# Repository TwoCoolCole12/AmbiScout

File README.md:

# AmbiScout
A portable environment sensor to sense ambient temperature, humidity, light, movement speed, and more!

Inspired by features on the Starbie, but extended for functionality and development time. 

Living in a place where the climate constantly fluctuates, it can be handy to glance at a small device that's 
not a phone to see what's happening in the air around oneself.

Here's some of the planned features:

- [x] Temperature Sensor
- [x] Humidity Sensor
- [x] Battery Powered or Rechargeability
- [x] OLED Display
- [x] Navigation Buttons
- [x] Power/Charging Indicator
- [x] Ambient Light Level Monitor
- [x] Audio Sensor

Checks does not mean it's programmed, just accounted for and wired.

With enough work, it might be reasonable to add in these features too, but they are lower priority:

- [ ] Wi-Fi Connection
- [ ] Bluetooth Compatiblitiy
- [ ] Access to Weather Forcasts
- [ ] Push Notifications when Major Changes Occue
- [ ] Charging & Battery Info
- [ ] CO2 Sensor
- [x] Barometric Pressure Sensor
- [ ] Built in Clock
- [ ] Movement Sensor

**Hardware Specifications** WIP

* Espressif ESP32-S3-MINI-1-N8 - Chosen due to high pin number, Wi-Fi and Bluetooth connectivity, compatibility with Arduino, and low cost for the given performance
  * Pin Layout Reference: https://documentation.espressif.com/esp32-s3-mini-1_mini-1u_datasheet_en.html
* Light Dependent Resistor A1050 14 - Selected due to native support in KiCad and high sensitivity
  * Pin Reference: https://www.caretxdigital.com/cat6-ethernet-cable-amazon/
* I2C SHT31-DIS Temperature & Humidity Sensor - Chosen due to accuracy and multifunctionality
  * Pin Reference: https://www.alldatasheet.com/datasheet-pdf/view/1522466/SENSIRION/SHT31-DIS.html
* SPH0655LM4H-1-8 Sound Sensor - Chosen for compactness and price point
  * Pin Reference: https://mm.digikey.com/Volume0/opasdata/d220001/medias/docus/6634/SPH0655LM4H-1-8.pdf

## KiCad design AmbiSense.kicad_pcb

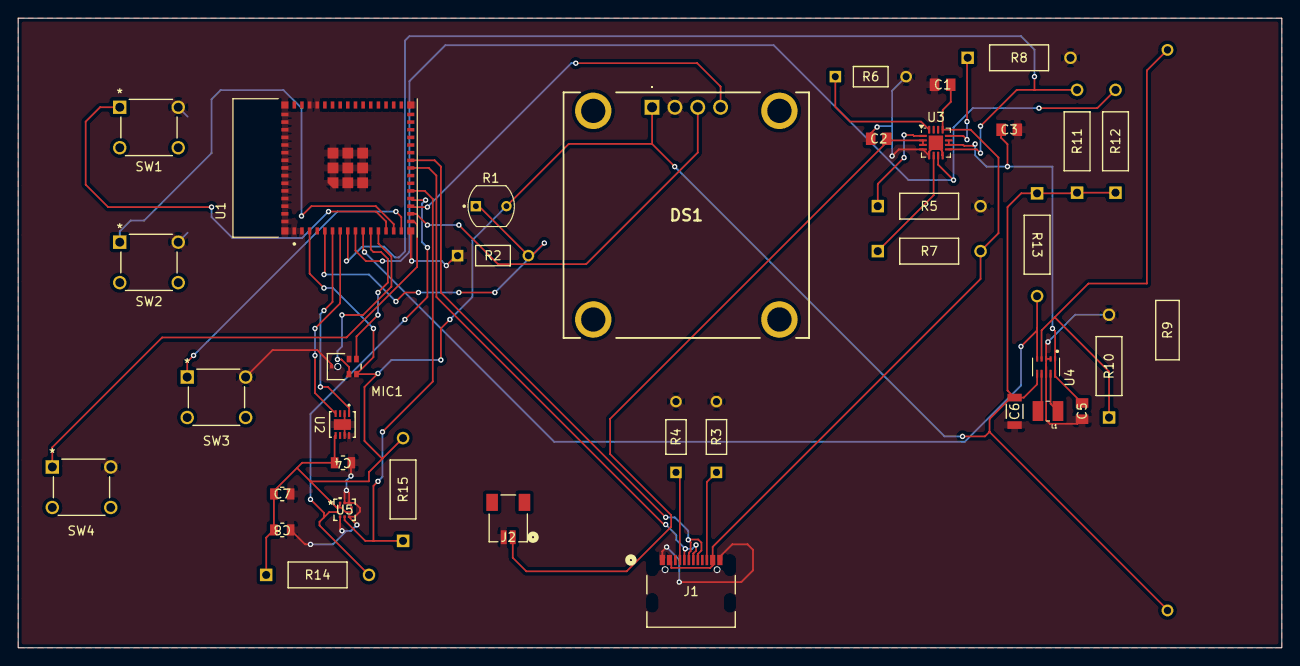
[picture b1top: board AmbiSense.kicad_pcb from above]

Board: 2 copper layers, 140.5 x 70.0 mm, 37 parts (0 on the bottom side), 32 nets.

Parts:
C1, C2, C3, C5: 10µF; Cap10UF
C4, C7, C8: 100nF; Cap100nF
C6: 22µF; Cap22UF
DS1: WEA012864DWPP3N00003
J1: USB4105-GF-A; USB4105_GCT
J2: SM02B-SRSS-TB LFSN; CONN_SM02B-SRSS-TB_JST
L1: 0.47 µH; INDC2520X120N
MIC1: SPH0655LM4H-1; SPH0655LM4H-1_KNO
R1: PDV-P8103; PHODET_PDV-P8103
R2: 100K; Res100kO
R3, R4: 5.1K; Res5.1kO
R5, R7, R11, R12, R13: 10k; Res10kO
R6: 1.8k; Res1.8kO
R8: 3k; Res3kO
R9: 511k; Res511kO
R10: 91k; Res91kO
R14, R15: 4.7kΩ; Res4.7kO
SW1, SW2, SW3, SW4: SW_Push; SW4_1825910-B_TEC
U1: ESP32-S3-MINI-1-N8; XCVR_ESP32-S3-MINI-1-N8
U2: SHT31-DIS; U_SHT3_SEN
U3: BQ24074RGT; VQFN-16-1EP_3x3mm_P0.5mm_EP1.6x1.6mm
U4: TPS63802DLAR; VREG_TPS63802DLAR
U5: BMP384; LGA10_2.0X2.0X0.95_BOS

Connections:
/3V3_POWER: C4.2, C6.2, C7.1, C8.2, DS1.1 (VCC), MIC1.5 (VDD), R1.2, R9.1, R11.1, R12.1, R13.1, R14.1, R15.2, U1.3 (3V3), U2.5 (VDD), U4.6 (VOUT), U5.1 (VDDIO), U5.6 (CSB), U5.10 (VDD)
/AUDIO_CLOCK: MIC1.4 (CLOCK), U1.12 (IO8)
/AUDIO_DATA: MIC1.1 (DATA), U1.11 (IO7)
/BAT_POS: C2.2, J2.1, U3.2 (BAT), U3.3 (BAT)
/BCK_SW: SW4.1, U1.16 (IO12)
/CHG STATUS: R11.2, U1.8 (IO4), U3.9 (~CHG)
/DOWN_SW: SW2.1, U1.14 (IO10)
/LDR_I/O: R1.1, R2.2, U1.5 (IO1)
/OLED_SCL: DS1.3 (SCL), U1.17 (IO13)
/OLED_SDA: DS1.4 (SDA), U1.18 (IO14)
/PGOOD STATUS: R12.2, U1.9 (IO5), U3.7 (~PGOOD)
/PRESS_SCL: R14.2, U1.19 (IO15), U5.2 (SCK)
/PRESS_SDA: R15.1, U1.20 (IO16), U5.4 (SDI)
/REG PGOOD: R13.2, U1.10 (IO6), U4.5 (PG)
/SEL_SW: SW3.1, U1.15 (IO11)
/SYS_PWR: C3.1, C5.2, U3.10 (OUT), U3.11 (OUT), U4.1 (EN), U4.10 (VIN)
/T&H SCL: U1.7 (IO3), U2.4 (SCL)
/T&H SDA: U1.6 (IO2), U2.1 (SDA)
/UP_SW: SW1.1, U1.13 (IO9)
/USB 5V: C1.2, J1.A4-B9 (VBUS), J1.B4-A9 (VBUS), R7.2, U3.13 (IN)
/USB D+: J1.A6 (DP1), J1.B6 (DP2), U1.24 (IO20)
/USB D-: J1.A7 (DN1), J1.B7 (DN2), U1.23 (IO19)
GND: C1.1, C2.1, C3.2, C4.1, C5.1, C6.1, C7.2, C8.1, DS1.2 (GND), J1.A1-B12 (GND), J1.B1-A12 (GND), J2.2, MIC1.3 (GROUND), R2.1, R3.2, R4.2, R5.2, R6.2, R8.2, R10.2, SW1.2, SW2.2, SW3.2, SW4.2, U1.1 (GND), U1.2 (GND), U1.42 (GND), U1.43 (GND), U1.46 (GND), U1.47 (GND), U1.48 (GND), U1.49 (GND), U1.50 (GND), U1.51 (GND), U1.52 (GND), U1.53 (GND), U1.54 (GND), U1.55 (GND), U1.56 (GND), U1.57 (GND), U1.58 (GND), U1.59 (GND), U1.60 (GND), U1.61 (GND), U1.61_1 (GND), U1.61_2 (GND), U1.61_3 (GND), U1.61_4 (GND), U1.61_5 (GND), U1.61_6 (GND), U1.61_7 (GND), U1.61_8 (GND), U1.62 (GND), U1.63 (GND), U1.64 (GND), U1.65 (GND), U2.2 (ADDR), U2.7 (R), U2.8 (VSS), U2.9 (VSS), U3.4 (~CE), U3.5 (EN2), U3.8 (VSS), U3.17 (VSS), U4.2 (MODE), U4.3 (AGND), U4.8 (GND), U5.3 (VSS), U5.5 (SDO), U5.8 (VSS), U5.9 (VSS)
unnamed: J1.A5 (CC1), R4.1
unnamed: J1.B5 (CC2), R3.1
unnamed: R7.1, U3.6 (EN1)
unnamed: R8.1, U3.12 (ILIM)
unnamed: R6.1, U3.16 (ISET)
unnamed: R5.1, U3.1 (TS)
unnamed: R9.2, R10.1, U4.4 (FB)
unnamed: L1.1, U4.9 (L1)
unnamed: L1.2, U4.7 (L2)

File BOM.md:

# AmbiScout – bill of materials

<!-- Generated by Half Life from project cmuzxkajc008201k9c68hd4dr. Edits here are overwritten on the next sync. -->
<!-- Generated: 2026-10-10T14:32:10.378Z -->

> [!NOTE]
> This parts list is mirrored from [Half Life](https://halflife.hackclub.com). Editing it here will not change the platform's copy, and the next sync overwrites this file.

| Week | Tier | Parts funding |
| --- | --- | --- |
| Week 1 | Tier 2 | $65.00 |

| Part | What it's for | Qty | Unit | Total | Vendor |
| --- | --- | --- | --- | --- | --- |
| [ESP32-S3-MINI-1-N8](https://www.digikey.com/en/products/detail/espressif-systems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 | Microcontroller as the Main Brain, Wi-Fi and Bluetooth support | 1 | $5.43 | $5.43 | [DigiKey](https://www.digikey.com/en/products/detail/espressif-systems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 |
| [SHT31-DIS-B2.5KS](https://www.digikey.com/en/products/detail/sensirion-ag/SHT3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 | Temperature & Humidity Sensor | 1 | $5.00 | $5.00 | [DigiKey](https://www.digikey.com/en/products/detail/sensirion-ag/SHT3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 |
| [WEA012864DBPP3N00003](https://www.digikey.com/en/products/detail/winstar-display/W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 | OLED Display Screen | 1 | $7.82 | $7.82 | [DigiKey](https://www.digikey.com/en/products/detail/winstar-display/W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 |
| [TPS63802DLAR](https://www.digikey.com/en/products/detail/texas-instruments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 | Voltage Regulation when Powered by USB-C | 1 | $3.40 | $3.40 | [DigiKey](https://www.digikey.com/en/products/detail/texas-instruments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 |
| [BQ24074RGTR](https://www.digikey.com/en/products/detail/texas-instruments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 | Battery Charging | 1 | $2.43 | $2.43 | [DigiKey](https://www.digikey.com/en/products/detail/texas-instruments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 |
| [SPH0655LM4H-1-8](https://www.digikey.com/en/products/detail/syntiant/SPH0655L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 | Audio Level Sensor | 1 | $1.69 | $1.69 | [DigiKey](https://www.digikey.com/en/products/detail/syntiant/SPH0655L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 |
| [CF18JT5K10](https://www.digikey.com/en/products/detail/stackpole-electro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 | 5.1kΩ Resistor | 2 | $0.10 | $0.20 | [DigiKey](https://www.digikey.com/en/products/detail/stackpole-electro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 |
| [CF14JT3K00](https://www.digikey.com/en/products/detail/stackpole-electro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 | 3kΩ Resistor | 1 | $0.10 | $0.10 | [DigiKey](https://www.digikey.com/en/products/detail/stackpole-electro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 |
| [CF18JT1K80](https://www.digikey.com/en/products/detail/stackpole-electro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 | 1.8kΩ Resistor | 1 | $0.10 | $0.10 | [DigiKey](https://www.digikey.com/en/products/detail/stackpole-electro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 |
| [CF14JT91K0](https://www.digikey.com/en/products/detail/stackpole-electro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 | 91kΩ Resistor | 1 | $0.10 | $0.10 | [DigiKey](https://www.digikey.com/en/products/detail/stackpole-electro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 |
| [RNF14FTD511K](https://www.digikey.com/en/products/detail/stackpole-electro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 | 511kΩ Resistor | 1 | $0.10 | $0.10 | [DigiKey](https://www.digikey.com/en/products/detail/stackpole-electro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 |
| [CL21B106KOQNNNE](https://www.digikey.com/en/products/detail/samsung-electro-m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 | 10μF Capacitor | 4 | $0.27 | $1.08 | [DigiKey](https://www.digikey.com/en/products/detail/samsung-electro-m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 |
| [CL31A226KPHNNNE](https://www.digikey.com/en/products/detail/samsung-electro-m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 | 22μF Capacitor | 1 | $0.47 | $0.47 | [DigiKey](https://www.digikey.com/en/products/detail/samsung-electro-m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 |
| [CL21B104KBCNNNC](https://www.digikey.com/en/products/detail/samsung-electro-m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 | 100nF Capacitor | 3 | $0.10 | $0.30 | [DigiKey](https://www.digikey.com/en/products/detail/samsung-electro-m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 |
| [1825910-6](https://www.digikey.com/en/products/detail/te-connectivity-a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 | Navigation Buttons | 4 | $0.13 | $0.52 | [DigiKey](https://www.digikey.com/en/products/detail/te-connectivity-a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 |
| [SM02B-SRSS-TB](https://www.digikey.com/en/products/detail/jst-sales-america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 | Battery Connector | 1 | $0.38 | $0.38 | [DigiKey](https://www.digikey.com/en/products/detail/jst-sales-america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 |
| [BMP384](https://www.digikey.com/en/products/detail/bosch-sensortec/B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 | Barometric Pressure Sensor | 1 | $3.81 | $3.81 | [DigiKey](https://www.digikey.com/en/products/detail/bosch-sensortec/B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 |
| [PDV-P8103](https://www.digikey.com/en/products/detail/advanced-photonix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 | Photoresistor | 1 | $0.72 | $0.72 | [DigiKey](https://www.digikey.com/en/products/detail/advanced-photonix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 |
| [MAMK2520HR47M](https://www.digikey.com/en/products/detail/taiyo-yuden/MAMK2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 | Inductor for the Regulator | 1 | $0.19 | $0.19 | [DigiKey](https://www.digikey.com/en/products/detail/taiyo-yuden/MAMK2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 |
| [USB4105-GF-A](https://www.digikey.com/en/products/detail/gct/USB4105-GF-A/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 | USB-C Receptacle for Data Transfer & Power | 1 | $0.80 | $0.80 | [DigiKey](https://www.digikey.com/en/products/detail/gct/USB4105-GF-A/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 |
| **Parts subtotal** | — | — | — | **$34.64** | — |
| **Tax & shipping** | — | — | — | **$12.13** | — |
| **Total** | — | — | — | **$46.77** | — |

$18.23 left of the tier's funding.
